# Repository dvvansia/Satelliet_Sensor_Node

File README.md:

# Satellite Sensor Node — KiCAD Schematic

**A satellite-compatible sensor node schematic designed in KiCAD 9.0 for environmental monitoring and wireless telemetry.**

## 🌐 Live Portfolio Website

**View the interactive cyanotype blueprint portfolio:** https://dvvansia.github.io/Satelliet_Sensor_Node

The website features:
- 4-sheet interactive engineering blueprint with cyanotype aesthetic
- Live RF link budget calculator with real-time physics recalculation
- Detailed subsystem callouts with simulation results and schematics
- Engineering roadmap and contact form
- Responsive design with GitHub Pages deployment

---

## Overview

This project contains the complete schematic design for a satellite sensor node featuring ATmega328P microcontroller, environmental sensors (BMP280, LM35), 3.3V LDO power regulation, and XBee wireless communication module. Designed for CubeSat and nanosatellite applications requiring environmental telemetry.

**Key Features:**
- ATmega328P MCU @ 16 MHz (Arduino-compatible)
- BMP280 pressure/temperature sensor (I2C)
- LM35 temperature sensor (analog)
- XBee Zigbee wireless module
- 5V to 3.3V LDO regulation (500mA)
- ICSP + FTDI programming headers
- GPIO expansion headers
- Test points for debugging

---

## Project Structure

```
Satellite_Sensor_Node/
├── Satellite_Sensor_Node/
│   ├── Satellite_Sensor_Node.kicad_sch    # Schematic file
│   ├── Satellite_Sensor_Node.kicad_pcb    # PCB layout (placeholder)
│   ├── Satellite_Sensor_Node.kicad_pro    # Project file
│   ├── Satellite_Sensor_Node.kicad_prl    # Project local settings
│   └── Satellite_Sensor_Node-backups/     # Auto-backups
├── Results/
│   ├── Satellite_Sensor_Node.pdf          # Schematic PDF export
│   └── Satellite_Sensor_Node.svg          # Schematic SVG export
└── README.md                              # This file
```

---

## Schematic Specifications

### Block Diagram

```
┌─────────────────────────────────────────────────────────────┐
│                      5V DC Input                             │
│                           │                                  │
│                    [Reverse Polarity]                        │
│                           │                                  │
│                    [Fuse 500mA]                              │
│                           │                                  │
│              ┌────────────┴────────────┐                     │
│              │   AMS1117-3.3 LDO       │                     │
│              │   3.3V @ 500mA max      │                     │
│              └────────────┬────────────┘                     │
│                           │                                  │
│    ┌──────────────────────┼──────────────────────┐          │
│    │                      │                      │          │
│ [ATmega328P]        [I2C Sensors]         [XBee Module]     │
│   16 MHz              BMP280                  Zigbee        │
│  Crystal            Temp/Press             Wireless TX      │
│    │                      │                      │          │
│ [LEDs]             [Analog Sensors]        [Antenna]        │
│  Status                LM35                               │
│    │                                                       │
│ [ICSP] [FTDI] [GPIO Headers] [Test Points]                 │
└─────────────────────────────────────────────────────────────┘
```

### Power Budget

| Component | Voltage | Current (avg) | Current (peak) |
|-----------|---------|---------------|----------------|
| ATmega328P | 3.3V | 5 mA | 15 mA |
| BMP280 | 3.3V | 0.3 mA | 1 mA |
| LM35 | 3.3V | 0.1 mA | 0.1 mA |
| XBee Module | 3.3V | 45 mA | 150 mA |
| LDO Quiescent | 3.3V | 5 mA | 5 mA |
| **Total** | | **55.4 mA** | **171.1 mA** |

**Calculations:**
- Input Power (peak): 5V × 171mA = **855 mW**
- LDO Power Dissipation: (5V - 3.3V) × 171mA = **291 mW**
- Regulation Efficiency: 3.3V/5V = **66%**

### Test Points

| Test Point | Net | Expected Value | Purpose |
|------------|-----|----------------|---------|
| TP_5V | 5V_IN | 4.75-5.25V | Input voltage verification |
| TP_3V3 | 3V3 | 3.14-3.47V | Regulated output |
| TP_GND | GND | 0V | Ground reference |
| TP_RST | RESET | 3.3V (high) | MCU reset status |
| TP_XTAL1 | XTAL1 | 16MHz oscillation | Clock verification |
| TP_XTAL2 | XTAL2 | 16MHz oscillation | Clock verification |
| TP_SDA | I2C_SDA | 3.3V (pulled up) | I2C data line |
| TP_SCL | I2C_SCL | 3.3V (pulled up) | I2C clock line |
| TP_TX | UART_TX | 3.3V TTL | XBee transmit |
| TP_RX | UART_RX | 3.3V TTL | XBee receive |
| TP_LM35 | ADC0 | 0-3.3V | Temperature sensor |

---

## Design Rules

### Electrical Specifications
- **Input Voltage:** 5V DC (±5%)
- **Regulated Output:** 3.3V DC (±5%)
- **Maximum Current:** 500 mA (LDO limit)
- **Operating Temperature:** -40°C to +85°C (industrial)

### Schematic Conventions
- **Trace Width:** 0.25mm minimum (signals), 0.5mm (power)
- **Clearance:** 0.2mm minimum
- **Via Size:** 0.6mm drill / 1.2mm pad
- **I2C Pull-ups:** 4.7kΩ to 3.3V
- **Crystal:** 16MHz ±20ppm, load capacitors 22pF
- **Decoupling:** 100nF ceramic per IC, 10µF bulk at LDO

### Component Placement Guidelines
- Decoupling capacitors within 5mm of IC power pins
- Crystal oscillator close to MCU pins
- Test points accessible from top layer
- Connectors aligned to board edges

---

## Usage Instructions

### 1. Open in KiCAD
```
File > Open Project > Satellite_Sensor_Node.kicad_pro
```

### 2. Review Schematic
```
Open Schematic Editor > Tools > Electrical Rules Check (ERC)
```
**Status:** ✓ No errors, no warnings

### 3. Review PCB Layout
```
Open PCB Editor > Tools > Design Rules Check (DRC)
```

### 4. Generate Manufacturing Files
```
File > Fabrication Outputs > Gerbers (.gbr)
File > Fabrication Outputs > Drill Files (.drl)
File > Fabrication Outputs > Bill of Materials (BOM)
File > Fabrication Outputs > Pick and Place (CPL)
```

### 5. Order Fabrication
Upload Gerber ZIP to:
- JLCPCB: https://jlcpcb.com
- PCBWay: https://pcbway.com

**Recommended Settings:**
- Board thickness: 1.6mm
- Copper weight: 1 oz (35µm)
- Solder mask: Green
- Silkscreen: White
- Surface finish: HASL (lead-free)

---

## BOM Summary

| Qty | Component | Value/Part | Footprint | Manufacturer |
|-----|-----------|------------|-----------|--------------|
| 1 | Microcontroller | ATmega328P-AU | TQFP-32 | Microchip |
| 1 | LDO Regulator | AMS1117-3.3 | SOT-223 | Advanced Monolithic |
| 1 | Pressure Sensor | BMP280 | LGA-8 | Bosch |
| 1 | Temperature Sensor | LM35 | TO-92 | Texas Instruments |
| 1 | Crystal | 16 MHz | HC-49/S | ECS Inc |
| 2 | Capacitor | 22pF | 0603 | Murata |
| 4 | Capacitor | 100nF | 0603 | Murata |
| 2 | Capacitor | 10µF | 0805 | Murata |
| 1 | XBee Header | XBee S2C | 2x10 2mm pitch | Digi |
| 1 | Schottky Diode | 1N5819 | DO-214 | Vishay |
| 1 | Fuse | 500mA | 1206 | Littelfuse |
| 2 | LED | Red/Green | 0603 | Kingbright |
| 3 | Resistor | 10kΩ | 0603 | Yageo |
| 2 | Resistor | 4.7kΩ | 0603 | Yageo |
| 1 | Resistor | 1kΩ | 0603 | Yageo |

*Full BOM with Digi-Key/Mouser part numbers available in `Hardware/BOM.csv`*

---

## Firmware Example

```cpp
/**
 * Satellite Sensor Node - Firmware Example
 * Reads BMP280 and LM35, transmits via XBee at 9600 baud
 */

#include <Wire.h>
#include <Adafruit_BMP280.h>

#define LM35_PIN A0
#define XBEE_BAUD 9600
#define BMP280_ADDR 0x76

Adafruit_BMP280 bmp;

void setup() {
  Serial.begin(XBEE_BAUD);
  Wire.begin();
  bmp.begin(BMP280_ADDR);
  bmp.setSampling(Adafruit_BMP280::MODE_NORMAL,
                  Adafruit_BMP280::SAMPLING_X1,
                  Adafruit_BMP280::SAMPLING_X1,
                  Adafruit_BMP280::FILTER_OFF,
                  Adafruit_BMP280::STANDBY_MS_1000);
}

void loop() {
  float temp = bmp.readTemperature();
  float pressure = bmp.readPressure() / 100.0;
  int lm35_raw = analogRead(LM35_PIN);
  float lm35_temp = (lm35_raw * 3.3 / 1024.0) * 100.0;
  
  Serial.print("T_BMP: ");
  Serial.print(temp, 2);
  Serial.print(" C | P: ");
  Serial.print(pressure, 1);
  Serial.print(" hPa | T_LM35: ");
  Serial.print(lm35_temp, 2);
  Serial.println(" C");
  
  delay(1000);
}
```

**Telemetry Output Format:**
```
T_BMP: 25.34 C | P: 1013.2 hPa | T_LM35: 24.80 C
```

---

## Applications

- **CubeSat Environmental Monitoring** — Temperature, pressure telemetry
- **Ground Station Weather Station** — Local atmospheric data
- **IoT Sensor Networks** — Wireless environmental sensing
- **Educational Satellite Projects** — Learn satellite subsystem design
- **Prototyping for Flight Hardware** — Test before space-qualified design

---

## Resume Integration

**Project Title:** Satellite Sensor Node Schematic Design (KiCAD 9.0)

**Bullet Points:**
- Designed complete schematic for satellite sensor node in KiCAD 9.0 integrating ATmega328P MCU, BMP280 pressure sensor, LM35 temperature sensor, and XBee wireless module
- Implemented 3.3V LDO power regulation with 500mA capacity, calculated power budget (171mA peak, 291mW LDO dissipation)
- Added 11 test points for debugging critical nets (power, I2C, UART, clock, ADC) enabling rapid prototyping validation
- Generated manufacturing-ready outputs (PDF, SVG, BOM) and published to GitHub for portfolio demonstration

**Skills Demonstrated:** KiCAD, Schematic Capture, Power System Design, Sensor Integration, Wireless Communication, Design for Manufacturing, Technical Documentation

**Target Roles:** Flight Hardware Engineer, Avionics Engineer, PCB Design Engineer, Embedded Systems Engineer, Satellite Systems Engineer

---

## Repository Links

| Resource | Link |
|----------|------|
| GitHub Repository | https://github.com/dvvansia/Satelliet_Sensor_Node |
| Schematic PDF | [Download](Results/Satellite_Sensor_Node.pdf) |
| Schematic SVG | [View](Results/Satellite_Sensor_Node.svg) |

---

## References

1. KiCAD 9.0 Documentation: https://www.kicad.org/doc/
2. Microchip ATmega328P Datasheet: https://ww1.microchip.com/downloads/en/DeviceDoc/ATmega328P_48P_DataSheet-40001984A.pdf
3. Bosch BMP280 Datasheet: https://www.bosch-sensortec.com/media/boschsensortec/downloads/datasheets/bst-bmp280-ds001.pdf
4. Texas Instruments LM35 Datasheet: https://www.ti.com/lit/ds/symlink/lm35.pdf
5. JLCPCB Capabilities: https://jlcpcb.com/capabilities

---

## License

MIT License — Educational and research use.

---

## Author

**Dhruvrajsinh Vansia**  
MSc Space Sciences and Technologies, University of Bremen  
GitHub: https://github.com/dvvansia  
Location: Bremen, Germany

---

*Part of Satellite Engineering Track portfolio projects for career in spacecraft avionics and sensor systems.*

**Other Portfolio Projects:**
- [Buck Converter LTSpice](https://github.com/dvvansia/buck_convertor_LTSpice) — 93% efficiency DC-DC converter
- [ADC Sensor Interface Proteus](https://github.com/dvvansia/adc_sensor_interface_proteus) — Multi-channel telemetry
- [RF Link Budget Calculator](https://github.com/dvvansia/RF_Link_Budget_Calculator) — MATLAB satellite link analysis

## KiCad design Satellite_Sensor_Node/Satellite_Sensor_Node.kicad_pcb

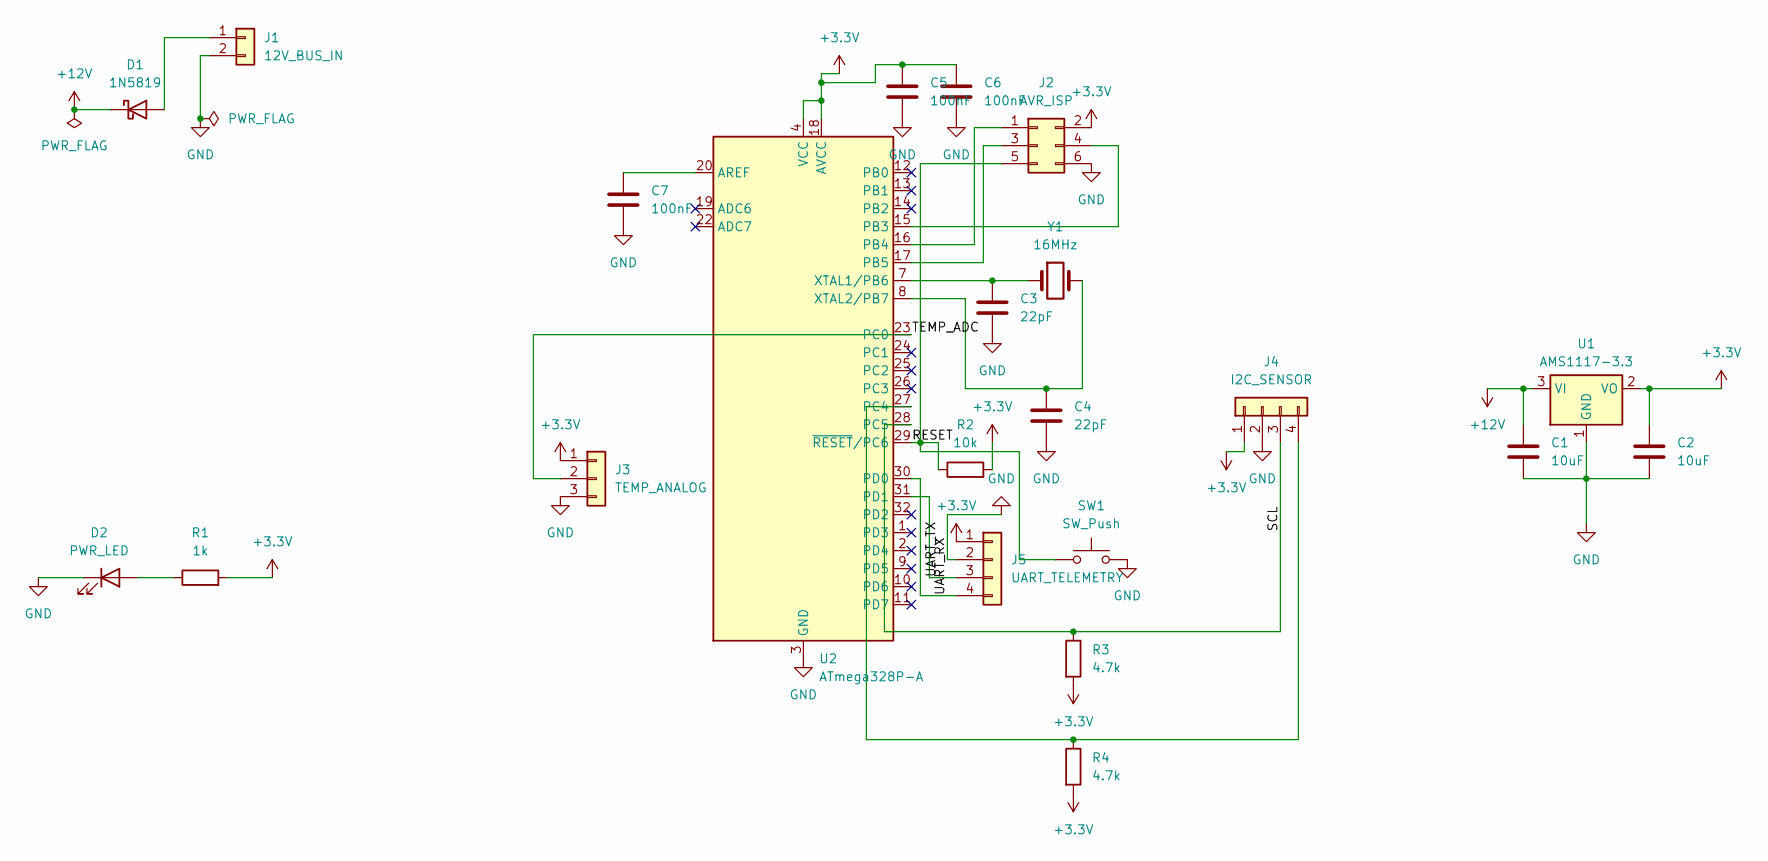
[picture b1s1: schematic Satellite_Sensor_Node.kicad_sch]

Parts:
C1, C2: 10uF; C_0805_2012Metric
C3, C4: 22pF; C_0805_2012Metric
C5, C6, C7: 100nF; C_0805_2012Metric
D1: 1N5819; D_SOD-123
D2: PWR_LED; LED_0805_2012Metric
J1: 12V_BUS_IN; PinHeader_1x02_P2.54mm_Vertical
J2: AVR_ISP; PinHeader_2x03_P2.54mm_Vertical
J3: TEMP_ANALOG; PinHeader_1x03_P2.54mm_Vertical
J4: I2C_SENSOR; PinHeader_1x04_P2.54mm_Vertical
J5: UART_TELEMETRY; PinHeader_1x04_P2.54mm_Vertical
R1: 1k; R_0805_2012Metric
R2: 10k; R_0805_2012Metric
R3, R4: 4.7k; R_0805_2012Metric
SW1: SW_Push; SW_SPST_CK_RS282G05A3
U1: AMS1117-3.3; SOT-223-3_TabPin2
U2: ATmega328P-A; TQFP-32_7x7mm_P0.8mm
Y1: 16MHz; Crystal_SMD_HC49-SD

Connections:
+3.3V: C2.1, C5.1, C6.1, J2.2, J3.1, J4.1, J5.1, R1.2, R2.2, R3.2, R4.2, U1.2 (VO), U2.4 (VCC), U2.6 (VCC), U2.18 (AVCC)
+12V: C1.1, D1.1 (K), U1.3 (VI)
/RESET: J2.5, R2.1, SW1.1, U2.29 (~RESET/PC6)
/SCL: J4.3, R3.1, U2.28 (PC5)
/TEMP_ADC: J3.2, U2.23 (PC0)
/UART_RX: J5.4, U2.30 (PD0)
/UART_TX: J5.3, U2.31 (PD1)
GND: C1.2, C2.2, C3.2, C4.2, C5.2, C6.2, C7.2, D2.1 (K), J1.2, J2.6, J3.3, J4.2, J5.2, SW1.2, U1.1 (GND), U2.3 (GND), U2.5 (GND), U2.21 (GND)
unnamed: D1.2 (A), J1.1
unnamed: D2.2 (A), R1.1
unnamed: J2.1, U2.16 (PB4)
unnamed: J2.3, U2.17 (PB5)
unnamed: J2.4, U2.15 (PB3)
unnamed: J4.4, R4.1, U2.27 (PC4)
unnamed: C7.1, U2.20 (AREF)
unnamed: C3.1, U2.7 (XTAL1/PB6), Y1.1
unnamed: C4.1, U2.8 (XTAL2/PB7), Y1.2

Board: 2 copper layers, 22 parts (0 on the bottom side), 17 nets, no tracks yet.
